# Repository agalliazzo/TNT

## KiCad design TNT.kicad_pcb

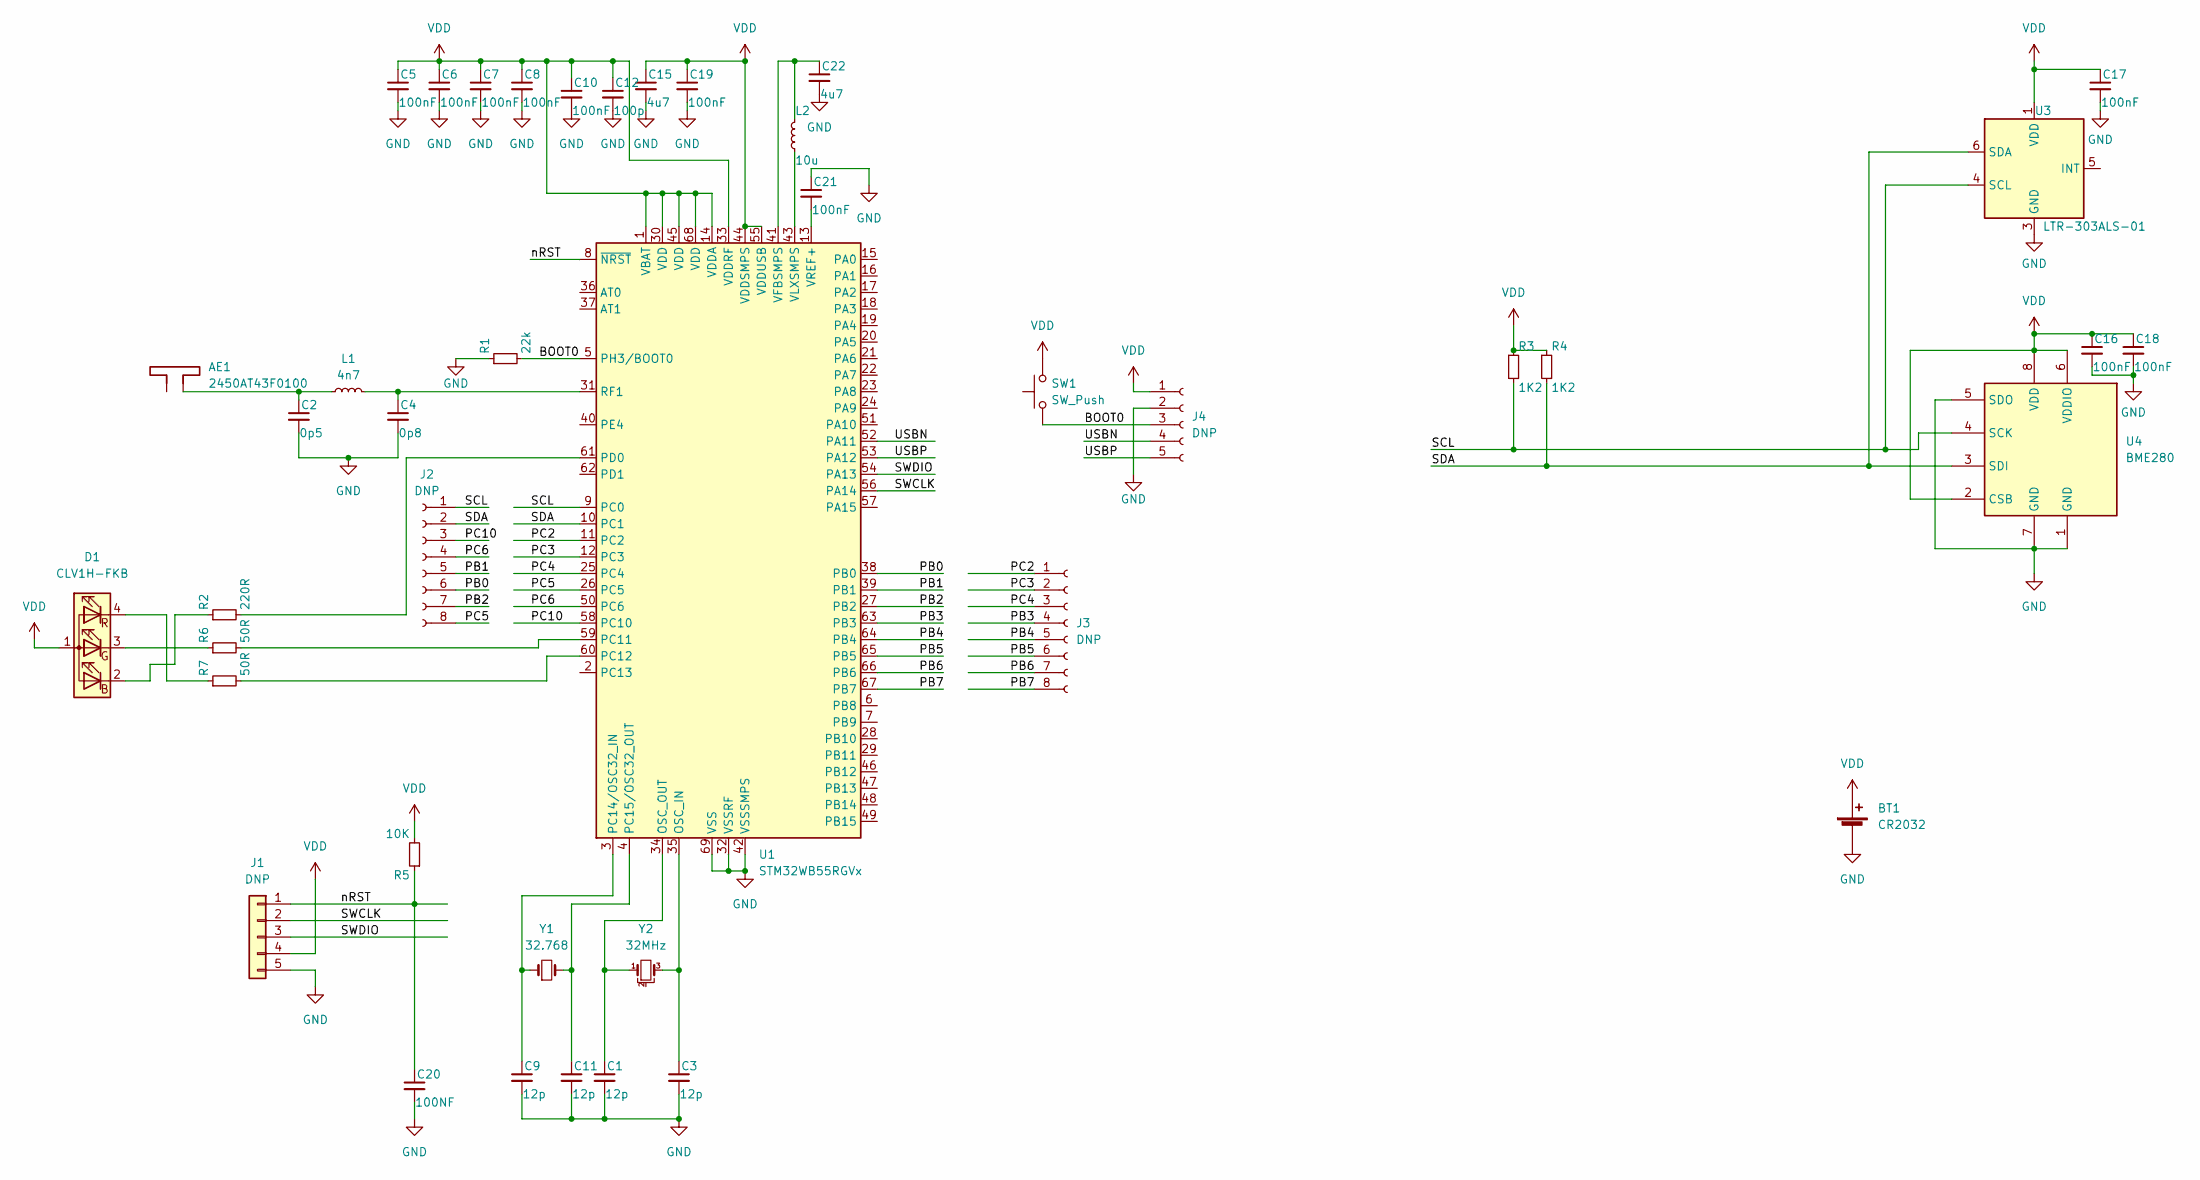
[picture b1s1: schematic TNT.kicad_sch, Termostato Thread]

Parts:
AE1: 2450AT43F0100; Johanson_2450AT43F0100
BT1: CR2032; BatteryHolder_Keystone_3002_1x2032_ALE
C1, C3, C9, C11: 12p; C_0603_1608Metric
C2: 0p5; C_0603_1608Metric
C4: 0p8; C_0603_1608Metric
C5, C6, C7, C8, C10, C16, C17, C18, C19, C21: 100nF; C_0603_1608Metric
C12: 100p; C_0603_1608Metric
C15, C22: 4u7; C_0603_1608Metric
C20: 100NF; C_0603_1608Metric
D1: CLV1H-FKB; LED_Cree-PLCC4_3.2x2.8mm_ale
J1: DNP; PinHeader_1x05_P1.27mm_Vertical
J2, J3: DNP; PinHeader_1x08_P2.00mm_Vertical
J4: DNP; PinHeader_1x05_P2.00mm_Vertical
L1: 4n7; L_0603_1608Metric
L2: 10u; L_0603_1608Metric
R1: 22k; R_0603_1608Metric
R2: 220R; R_0603_1608Metric
R3, R4: 1K2; R_0603_1608Metric
R5: 10K; R_0603_1608Metric
R6, R7: 50R; R_0603_1608Metric
SW1: SW_Push; SW_Push_1P1T_NO_Vertical_Wuerth_434133025816
U1: STM32WB55RGVx; QFN-68-1EP_8x8mm_P0.4mm_EP5.2x5.2mm
U3: LTR-303ALS-01; Lite-On_LTR-303ALS-01
U4: BME280; Bosch_LGA-8_2.5x2.5mm_P0.65mm_ClockwisePinNumbering
Y1: 32.768; Crystal_SMD_2012-2Pin_2.0x1.2mm
Y2: 32MHz; Crystal_SMD_2016-4Pin_2.0x1.6mm

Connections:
/BOOT0: J4.3, R1.2, SW1.1, U1.5 (PH3/BOOT0)
/PB0: J2.6, U1.38 (PB0)
/PB1: J2.5, U1.39 (PB1)
/PB2: J2.7, U1.27 (PB2)
/PB3: J3.4, U1.63 (PB3)
/PB4: J3.5, U1.64 (PB4)
/PB5: J3.6, U1.65 (PB5)
/PB6: J3.7, U1.66 (PB6)
/PB7: J3.8, U1.67 (PB7)
/PC2: J3.1, U1.11 (PC2)
/PC3: J3.2, U1.12 (PC3)
/PC4: J3.3, U1.25 (PC4)
/PC5: J2.8, U1.26 (PC5)
/PC6: J2.4, U1.50 (PC6)
/PC10: J2.3, U1.58 (PC10)
/SCL: J2.1, R3.2, U1.9 (PC0), U3.4 (SCL), U4.4 (SCK)
/SDA: J2.2, R4.2, U1.10 (PC1), U3.6 (SDA), U4.3 (SDI)
/SWCLK: J1.2, U1.56 (PA14)
/SWDIO: J1.3, U1.54 (PA13)
/USBN: J4.4, U1.52 (PA11)
/USBP: J4.5, U1.53 (PA12)
/nRST: C20.1, J1.1, R5.1, U1.8 (~NRST)
GND: BT1.2 (-), C1.2, C2.2, C3.2, C4.2, C5.2, C6.2, C7.2, C8.2, C9.2, C10.2, C11.2, C12.2, C15.2, C16.2, C17.2, C18.2, C19.2, C20.2, C21.1, C22.2, J1.5, J4.2, R1.1, U1.32 (VSSRF), U1.42 (VSSSMPS), U1.69 (VSS), U3.3 (GND), U4.1 (GND), U4.5 (SDO), U4.7 (GND)
unnamed: AE1.2, C2.1, L1.1
unnamed: C1.1, U1.34 (OSC_OUT), Y2.1
unnamed: C3.1, U1.35 (OSC_IN), Y2.3
unnamed: C4.1, L1.2, U1.31 (RF1)
unnamed: C9.1, U1.3 (PC14/OSC32_IN), Y1.1
unnamed: C11.1, U1.4 (PC15/OSC32_OUT), Y1.2
unnamed: C21.2, U1.13 (VREF+)
unnamed: C22.1, L2.2, U1.41 (VFBSMPS)
unnamed: D1.2 (BK), R2.1
unnamed: D1.3 (GK), R6.1
unnamed: D1.4 (RK), R7.1
unnamed: L2.1, U1.43 (VLXSMPS)
unnamed: R2.2, U1.61 (PD0)
unnamed: R6.2, U1.59 (PC11)
unnamed: R7.2, U1.60 (PC12)
VDD: BT1.1 (+), C5.1, C6.1, C7.1, C8.1, C10.1, C12.1, C15.1, C16.1, C17.1, C18.1, C19.1, D1.1 (A), J1.4, J4.1, R3.1, R4.1, R5.2, SW1.2, U1.1 (VBAT), U1.14 (VDDA), U1.30 (VDD), U1.33 (VDDRF), U1.44 (VDDSMPS), U1.45 (VDD), U1.55 (VDDUSB), U1.68 (VDD), U3.1 (VDD), U4.2 (CSB), U4.6 (VDDIO), U4.8 (VDD)

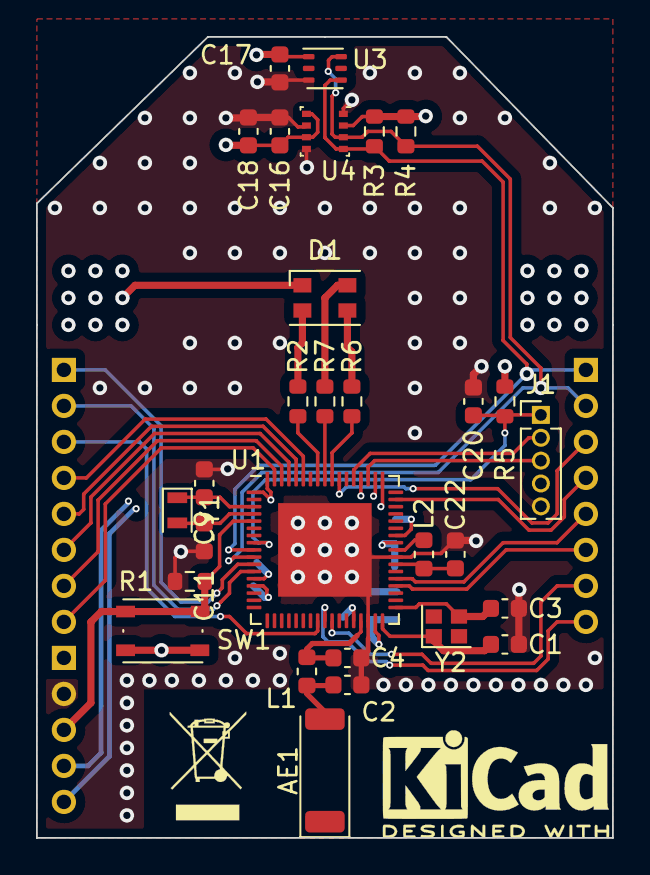
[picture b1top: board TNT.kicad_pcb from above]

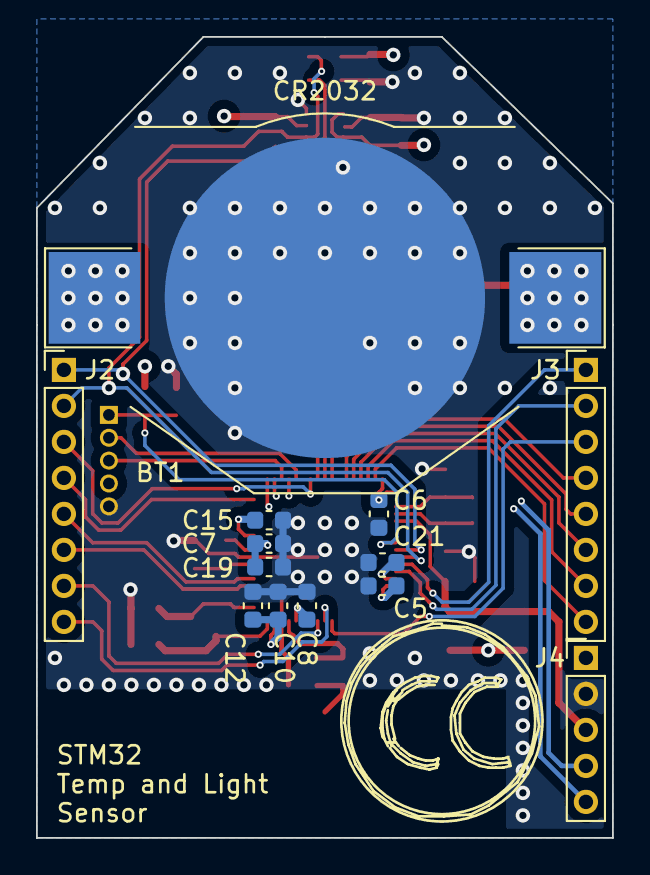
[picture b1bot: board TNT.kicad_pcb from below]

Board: 4 copper layers, 32.0 x 44.5 mm, 42 parts (13 on the bottom side), 39 nets.

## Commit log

2022-11-28 First release
